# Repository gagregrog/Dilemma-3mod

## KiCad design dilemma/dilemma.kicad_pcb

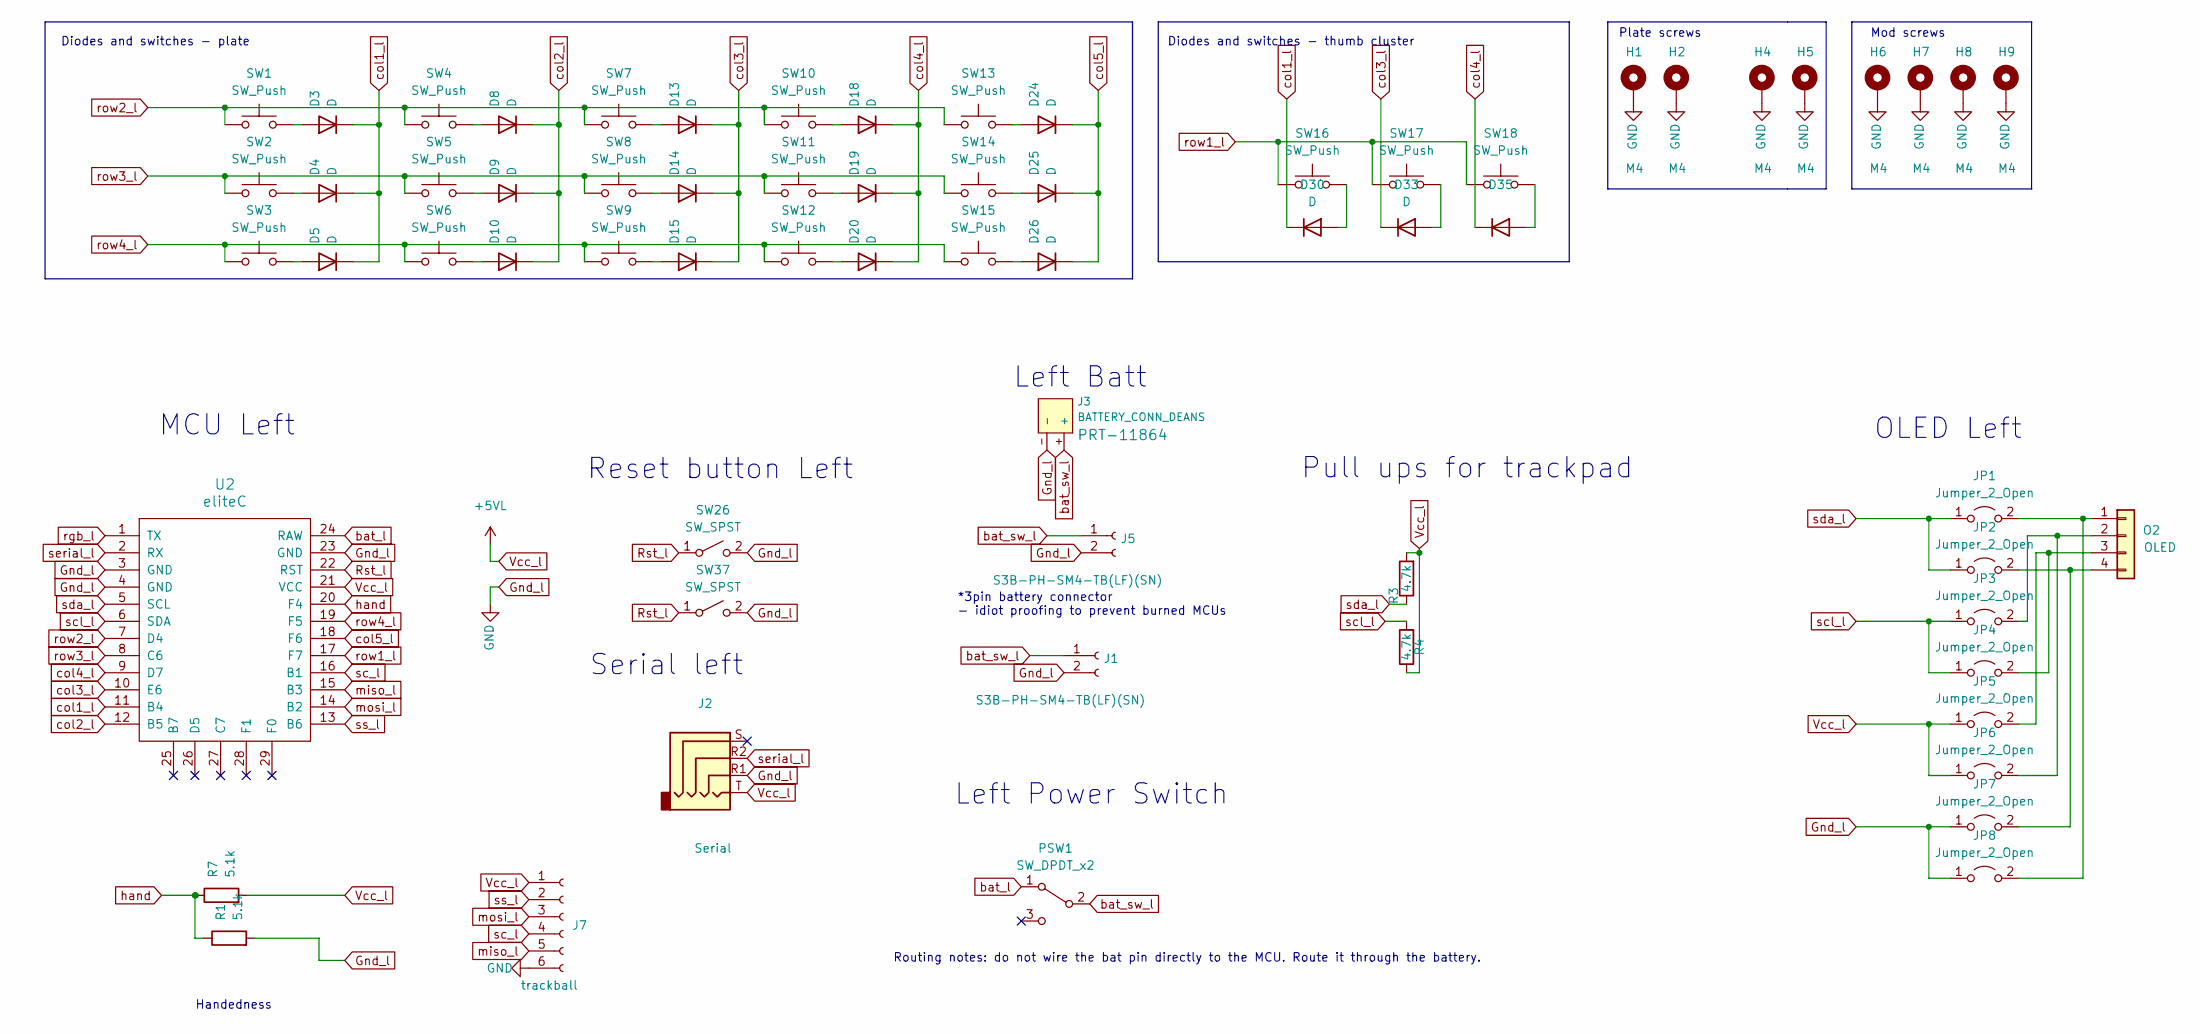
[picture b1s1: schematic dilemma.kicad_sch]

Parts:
D3, D4, D5, D8, D9, D10, D13, D14, D15, D18, D19, D20, D24, D25, D26, D30, D33: D
D35: (no value)
H1, H2, H4, H5, H6, H7, H8, H9: M4; MountingHole_3mm_Pad_thin
J1, J5: S3B-PH-SM4-TB(LF)(SN); JST_SH_BM02B-SRSS-TB_1x02-1MP_P1.00mm_Vertical; LCSC C265101
J2: Serial; Jack_3.5mm_PJ320E_Horizontal_reversible
J3: BATTERY_CONN_DEANS; battery_connector_THT
J7: trackball; 6_PinHeader
JP1, JP2, JP3, JP4, JP5, JP6, JP7, JP8: Jumper_2_Open; SolderJumper-2_P1.3mm_Open_RoundedPad1.0x1.5mm
O2: OLED; PinHeader_1x04_P2.54mm_Vertical
PSW1: SW_DPDT_x2; Switch_MSK-12C01-07; LCSC C431540
R1, R7: 5.1k; R_1206_handsolder; JLCPCB BOM 1
R3, R4: 4.7k; R_1206_handsolder_reversible; LCSC C269746
SW1, SW2, SW3, SW4, SW5, SW6, SW7, SW8, SW9, SW10, SW11, SW12, SW13, SW14, SW15, SW16, SW17, SW18: SW_Push; SW_MX_choc
SW26, SW37: SW_SPST; SW_Push_1P1T_NO_6x6mm_H9.5mm
U2: eliteC; pro-micro

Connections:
Gnd_l: H1.1, H2.1, H4.1, H5.1, H6.1, H7.1, H8.1, H9.1, J1.2, J2.R1, J3.-, J5.2, J7.6, JP7.1 (A), JP8.1 (A), R1.2, SW26.2 (B), SW37.2 (B), U2.3 (GND), U2.4 (GND), U2.23 (GND); also elsewhere on the board
unnamed: D3.2 (A), SW1.2
unnamed: D4.2 (A), SW2.2
unnamed: D5.2 (A), SW3.2
unnamed: D8.2 (A), SW4.2
unnamed: D9.2 (A), SW5.2
unnamed: D10.2 (A), SW6.2
unnamed: D13.2 (A), SW7.2
unnamed: D14.2 (A), SW8.2
unnamed: D15.2 (A), SW9.2
unnamed: D18.2 (A), SW10.2
unnamed: D19.2 (A), SW11.2
unnamed: D20.2 (A), SW12.2
unnamed: D24.2 (A), SW13.2
unnamed: D25.2 (A), SW14.2
unnamed: D26.2 (A), SW15.2
unnamed: D30.2 (A), SW16.2
unnamed: D33.2 (A), SW17.2
unnamed: D35.2 (A), SW18.2
unnamed: JP1.2 (B), JP8.2 (B), O2.1
unnamed: JP2.2 (B), JP7.2 (B), O2.4
unnamed: JP3.2 (B), JP6.2 (B), O2.2
unnamed: JP4.2 (B), JP5.2 (B), O2.3
Rst_l: SW26.1 (A), SW37.1 (A), U2.22 (RST)
Vcc_l: J2.T, J7.1, JP5.1 (A), JP6.1 (A), R3.2, R4.1, R7.2, U2.21 (VCC)
bat_l: PSW1.1 (A), U2.24 (RAW)
bat_sw_l: J1.1, J3.+, J5.1, PSW1.2 (B)
col1_l: D3.1 (K), D4.1 (K), D5.1 (K), D30.1 (K), U2.11 (B4)
col2_l: D8.1 (K), D9.1 (K), D10.1 (K), U2.12 (B5)
col3_l: D13.1 (K), D14.1 (K), D15.1 (K), D33.1 (K), U2.10 (E6)
col4_l: D18.1 (K), D19.1 (K), D20.1 (K), D35.1 (K), U2.9 (D7)
col5_l: D24.1 (K), D25.1 (K), D26.1 (K), U2.18 (F6)
hand: R1.1, R7.1, U2.20 (F4)
miso_l: J7.5, U2.15 (B3)
mosi_l: J7.3, U2.14 (B2)
rgb_l: U2.1 (TX)
row1_l: SW16.1, SW17.1, SW18.1, U2.17 (F7)
row2_l: SW1.1, SW4.1, SW7.1, SW10.1, SW13.1, U2.7 (D4)
row3_l: SW2.1, SW5.1, SW8.1, SW11.1, SW14.1, U2.8 (C6)
row4_l: SW3.1, SW6.1, SW9.1, SW12.1, SW15.1, U2.19 (F5)
sc_l: J7.4, U2.16 (B1)
scl_l: JP3.1 (A), JP4.1 (A), R4.2, U2.6 (SDA)
sda_l: JP1.1 (A), JP2.1 (A), R3.1, U2.5 (SCL)
serial_l: J2.R2, U2.2 (RX)
ss_l: J7.2, U2.13 (B6)

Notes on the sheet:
MCU Left
Left Batt
Handedness
Plate screws
Routing notes: do not wire the bat pin directly to the MCU. Route it through the battery.
Serial left
Diodes and switches - plate
Reset button Left
Pull ups for trackpad
Mod screws
Left Power Switch
OLED Left
Diodes and switches - thumb cluster
*3pin battery connector - idiot proofing to prevent burned MCUs

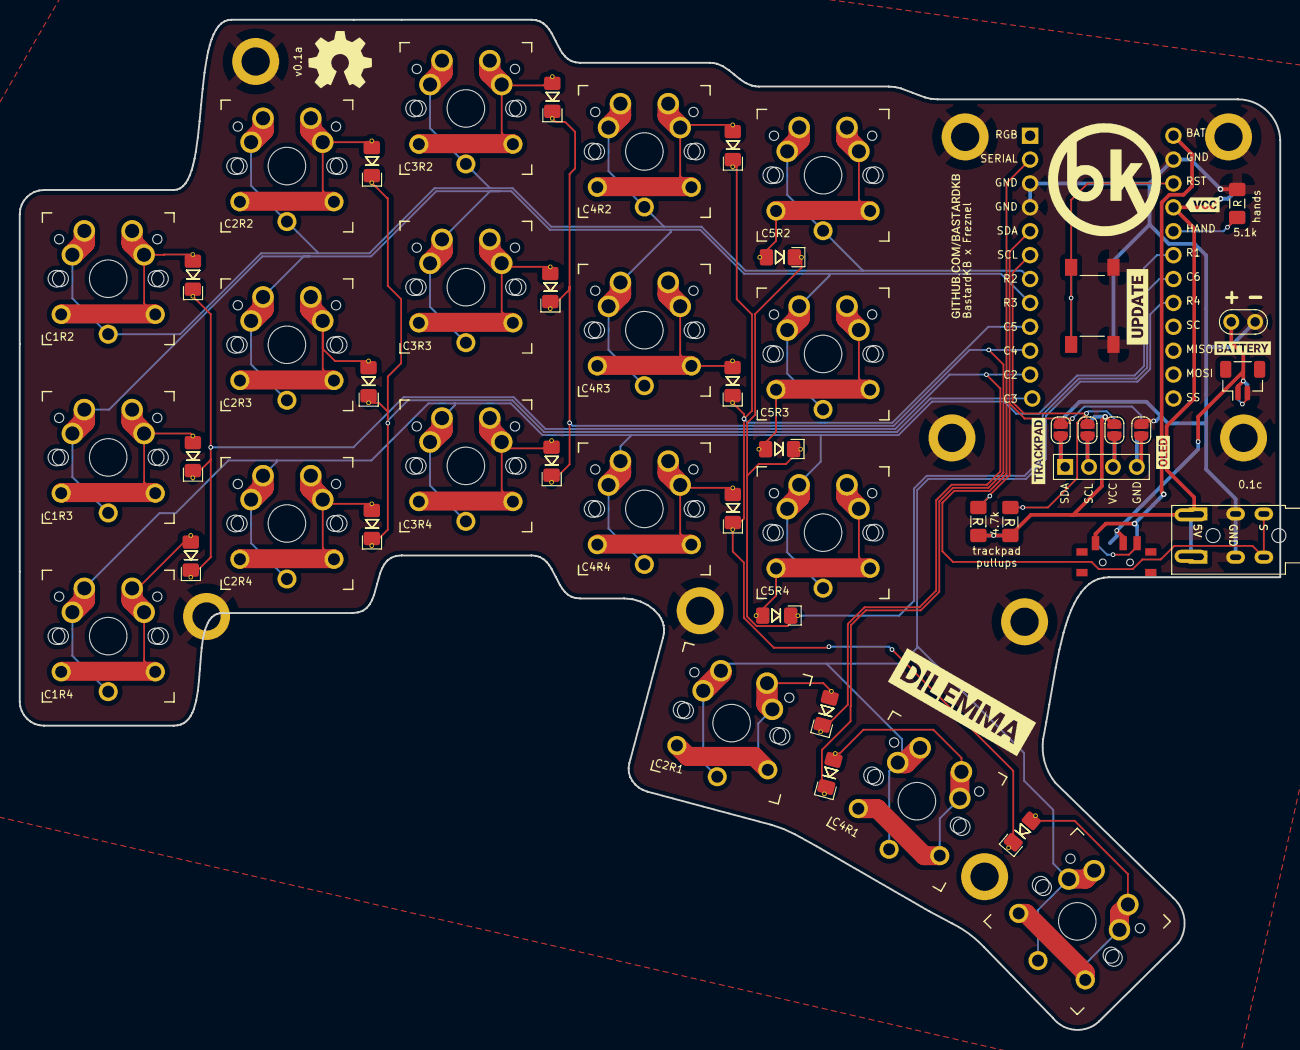
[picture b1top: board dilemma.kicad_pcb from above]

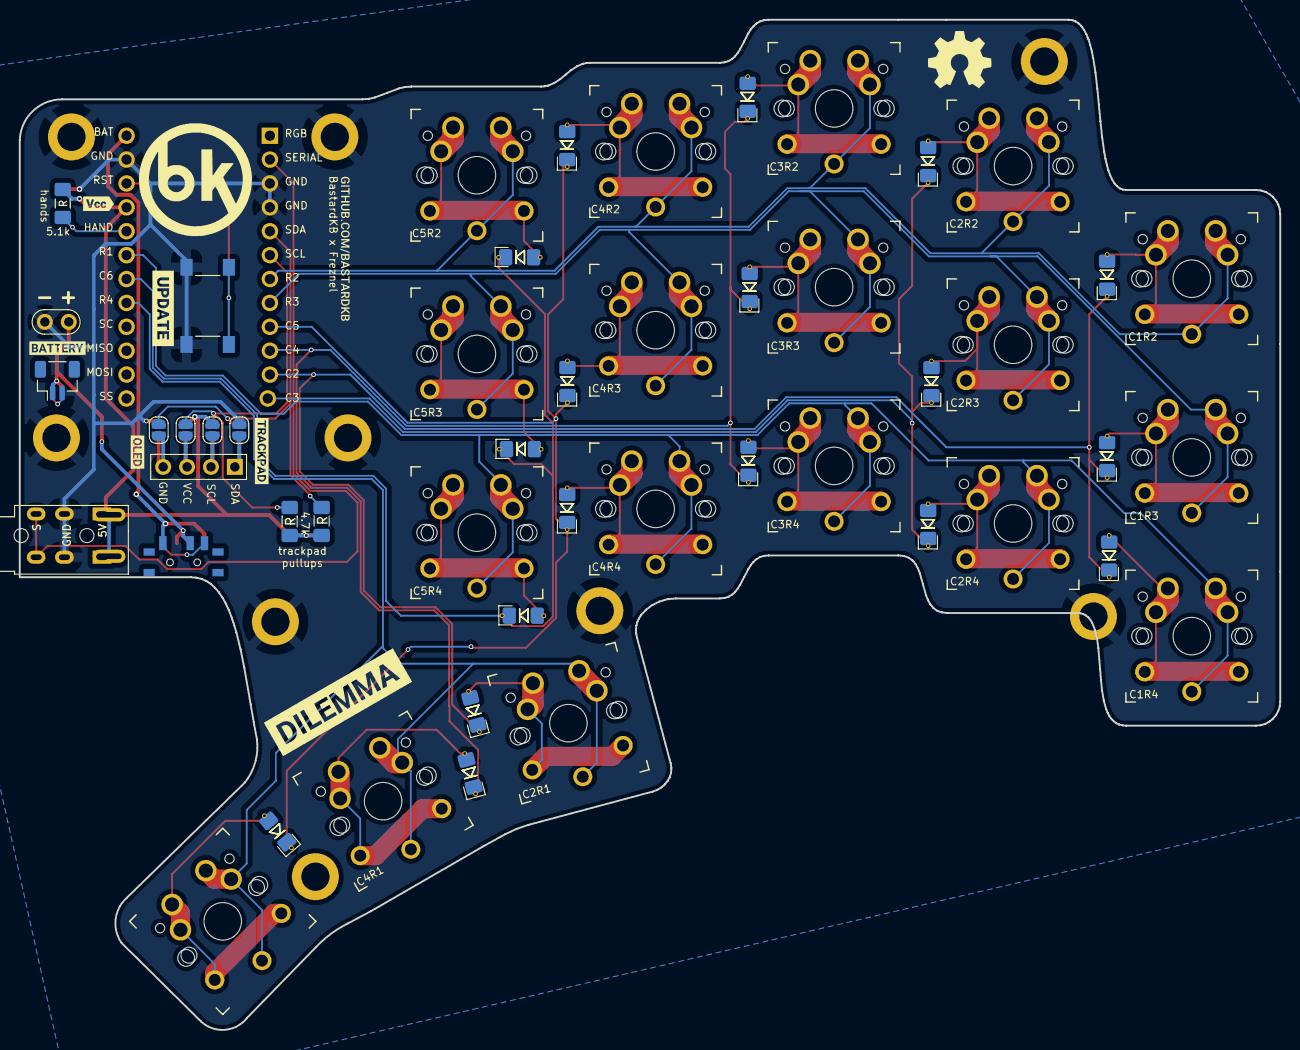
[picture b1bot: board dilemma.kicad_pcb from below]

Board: 2 copper layers, 134.0 x 107.4 mm, 80 parts (15 on the bottom side), 40 nets.

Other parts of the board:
H2#2: M4; MountingHole_3mm_Pad_thin
kibuzzard-61F01A92, kibuzzard-61F01A92#2: G***; kibuzzard-61F01A92
kibuzzard-61F01C84, kibuzzard-61F01C84#2: G***; kibuzzard-61F01C84
kibuzzard-628D3AA1: G***; kibuzzard-628D3AA1
kibuzzard-628D396A: G***; kibuzzard-628D396A
kibuzzard-628DFB5F, kibuzzard-628DFB5F#2: G***; kibuzzard-628DFB5F
kibuzzard-628DFB48, kibuzzard-628DFB48#2: G***; kibuzzard-628DFB48
kibuzzard-628DFB95, kibuzzard-628DFB95#2: G***; kibuzzard-628DFB95
kibuzzard-628E0199, kibuzzard-628E0199#2: G***; kibuzzard-628E0199

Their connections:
Gnd_l: H2#2.1; also elsewhere on the board

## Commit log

2022-07-27 added third thumb key in schematic and pcb layout
    firmware not touched yet, case and supporting objects not touched yet, gerbers expored in the dilemma subfolder
2022-08-03 mostly step and organization
2022-08-10 add splinky vial 3mod firmware to dilemma folder
2022-08-10 pull from main branch
2022-10-06 add modified thin case for 3mod
2023-07-09 feat: handwire v1
